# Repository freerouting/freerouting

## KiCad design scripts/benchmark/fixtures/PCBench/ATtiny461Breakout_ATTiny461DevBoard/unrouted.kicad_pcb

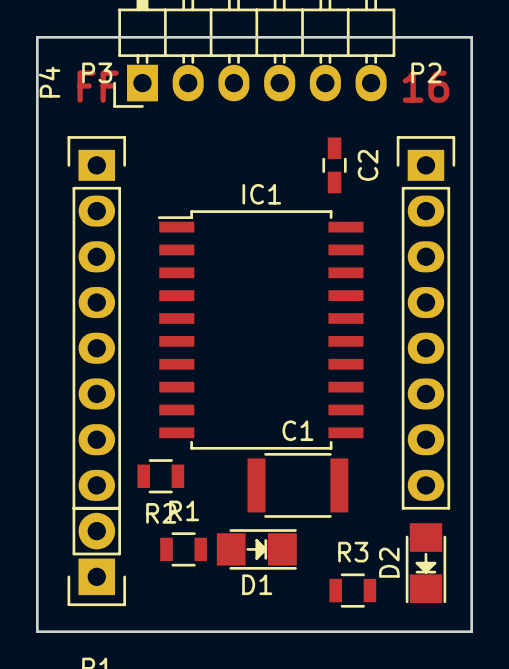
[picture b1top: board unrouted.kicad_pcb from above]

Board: 2 copper layers, 24.1 x 33.0 mm, 12 parts (0 on the bottom side), 20 nets, no tracks yet.

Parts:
C1: 10uF; C_1812
C2: 100nF; C_0603_HandSoldering
D1, D2: LED; LED_1206
IC1: ATTINY461-P; SOIC-20_7.5x12.8mm_Pitch1.27mm
P1: CONN_01X02; Pin_Header_Straight_1x02
P2, P3: CONN_01X08; Pin_Header_Straight_1x08
P4: CONN_01X06; Pin_Header_Angled_1x06
R1, R3: 1k; R_0805
R2: R; R_0805

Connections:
GND: C1.2, C2.2, D1.1, IC1.6, IC1.16, P1.1, P4.6, R3.1
unnamed: D1.2, R1.2
unnamed: D2.1, R3.2
unnamed: D2.2, IC1.11, P2.8
unnamed: IC1.1, P3.1, P4.3
unnamed: IC1.2, P3.2, P4.4
unnamed: IC1.3, P3.3, P4.5
unnamed: IC1.4, P3.4
unnamed: IC1.7, P3.5
unnamed: IC1.8, P3.6
unnamed: IC1.9, P3.7
unnamed: IC1.10, P3.8, P4.2, R2.1
unnamed: IC1.12, P2.7
unnamed: IC1.13, P2.6
unnamed: IC1.14, P2.5
unnamed: IC1.17, P2.4
unnamed: IC1.18, P2.3
unnamed: IC1.19, P2.2
unnamed: IC1.20, P2.1
VCC: C1.1, C2.1, IC1.5, IC1.15, P1.2, P4.1, R1.1, R2.2

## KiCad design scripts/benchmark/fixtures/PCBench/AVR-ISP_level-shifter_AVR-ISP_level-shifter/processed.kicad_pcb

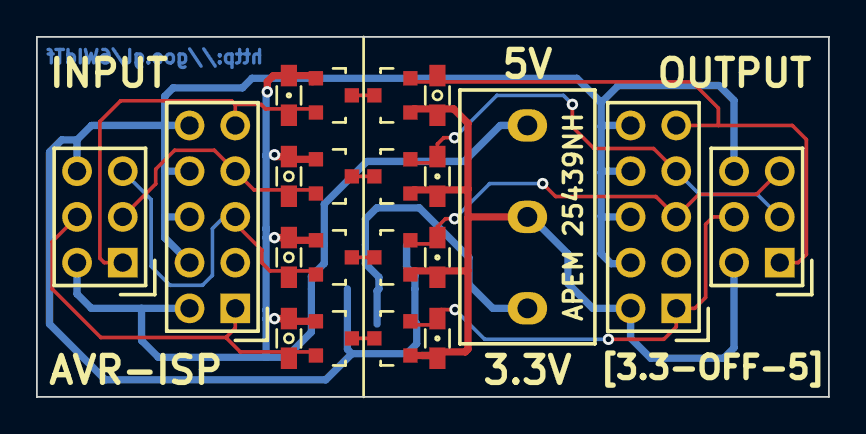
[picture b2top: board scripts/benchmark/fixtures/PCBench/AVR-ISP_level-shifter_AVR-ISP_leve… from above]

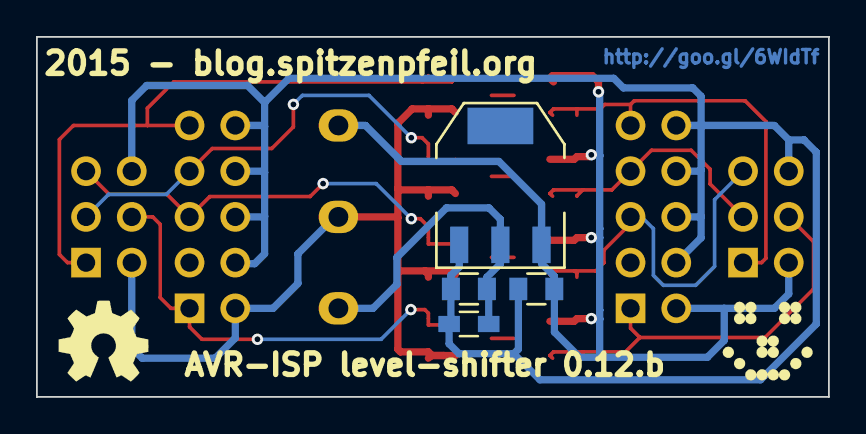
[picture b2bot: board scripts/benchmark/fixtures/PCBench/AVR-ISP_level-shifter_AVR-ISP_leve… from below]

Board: 2 copper layers, 44.0 x 20.0 mm, 27 parts (6 on the bottom side), 16 nets.

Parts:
C1, C2: 1µF; C_0805
DR.R2, DR.R3, DR.R5, DR.R7: 1K5; R_0603_HandSoldering
INPUT1: AVR-ISP-6; DIL-3
INPUT2: AVR-ISP-10; DIL-5
LOGO1: LED_smile_silkscreen_5mm
LOGO2: OSHW-logo_silkscreen_5mm
OUTPUT1: AVR-ISP-6; DIL-3
OUTPUT2: AVR-ISP-10; DIL-5
Q1, Q2, Q3, Q4, Q5, Q6, Q7, Q8: BSS138; SOT-23
R1, R4, R6, R8: 1K5; R_0603_HandSoldering
R9: 300R; R_0603_HandSoldering
SW1: APEM 25439NH; switch_vert_SPDT_ON-OFF-ON_TH_APEM-25439NH
U1: AMS1117-3.3; SOT-223

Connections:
/GND: C1.2, C2.2, INPUT1.6, INPUT2.4, INPUT2.6, INPUT2.8, INPUT2.10, OUTPUT1.6, OUTPUT2.4, OUTPUT2.6, OUTPUT2.8, OUTPUT2.10, R9.2, U1.1
/MISO_PRG: INPUT1.1, INPUT2.9, Q1.2, R1.2
/MISO_TARGET: DR.R2.2, OUTPUT1.1, OUTPUT2.9, Q2.2
/MOSI_PRG: DR.R7.2, INPUT1.4, INPUT2.1, Q7.2
/MOSI_TARGET: OUTPUT1.4, OUTPUT2.1, Q8.2, R8.2
/RESET_PRG: DR.R5.2, INPUT1.5, INPUT2.5, Q5.2
/RESET_TARGET: OUTPUT1.5, OUTPUT2.5, Q6.2, R6.2
/SCK_PRG: DR.R3.2, INPUT1.3, INPUT2.7, Q3.2
/SCK_TARGET: OUTPUT1.3, OUTPUT2.7, Q4.2, R4.2
/VCC_PRG: C1.1, DR.R3.1, DR.R5.1, DR.R7.1, INPUT1.2, INPUT2.2, Q1.1, Q3.1, Q5.1, Q7.1, R1.1, SW1.3, U1.3
/VCC_REG: C2.1, R9.1, SW1.1, U1.2
/VCC_TARGET: DR.R2.1, OUTPUT1.2, OUTPUT2.2, Q2.1, Q4.1, Q6.1, Q8.1, R4.1, R6.1, R8.1, SW1.2
unnamed: Q1.3, Q2.3
unnamed: Q3.3, Q4.3
unnamed: Q5.3, Q6.3
unnamed: Q7.3, Q8.3

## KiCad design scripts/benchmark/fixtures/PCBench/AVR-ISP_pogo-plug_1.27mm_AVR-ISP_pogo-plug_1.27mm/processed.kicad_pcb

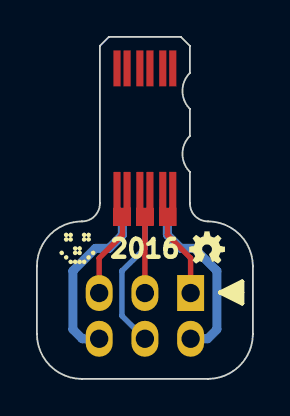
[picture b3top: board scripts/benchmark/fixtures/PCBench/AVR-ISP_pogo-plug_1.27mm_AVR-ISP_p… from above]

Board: 2 copper layers, 12.0 x 19.0 mm, 4 parts (0 on the bottom side), 6 nets.

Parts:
G1: LED_smile_silkscreen_2mm
G2: OSHW-logo_silkscreen_2mm
P1: CONN_6; MADW__PIN_ARRAY_3x2_2.54mm
P2: CONN_6; MADW__PIN_ARRAY_3x2_1.27mm

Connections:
/GND: P1.6, P2.6
/MISO: P1.1, P2.1
/MOSI: P1.4, P2.4
/RESET: P1.5, P2.5
/SCK: P1.3, P2.3
/V-target: P1.2, P2.2

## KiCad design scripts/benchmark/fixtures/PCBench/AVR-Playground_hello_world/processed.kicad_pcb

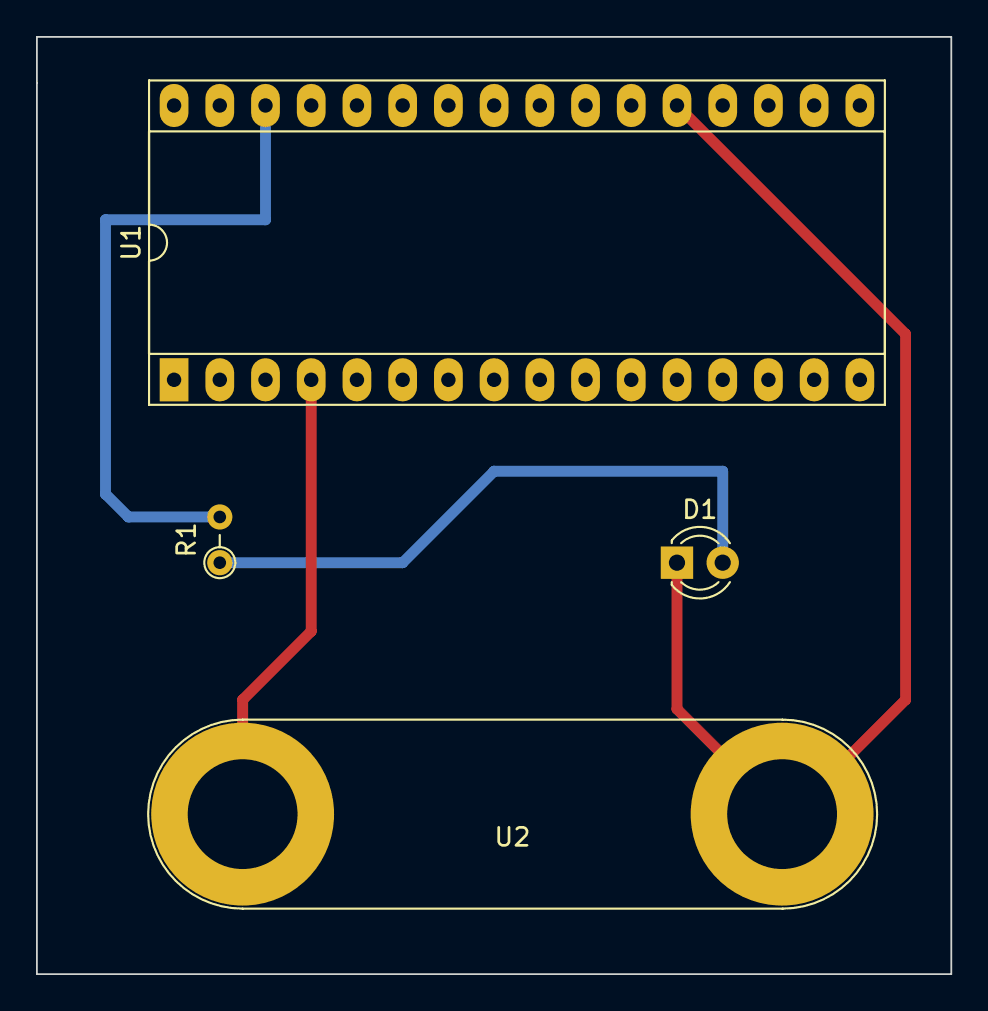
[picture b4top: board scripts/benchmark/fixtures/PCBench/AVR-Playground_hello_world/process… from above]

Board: 2 copper layers, 50.8 x 52.1 mm, 4 parts (0 on the bottom side), 4 nets.

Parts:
D1: LED; LED_D3.0mm
R1: 1k; R_Axial_DIN0204_L3.6mm_D1.6mm_P2.54mm_Vertical
U1: ATMEGA328P-AU; DIP-32_W15.24mm_Socket_LongPads
U2: myConn2; Banana_Jack_2Pin

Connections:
+5V: U1.4, U2.1
GND: D1.1, U1.21, U2.2
unnamed: D1.2, R1.1
unnamed: R1.2, U1.30
